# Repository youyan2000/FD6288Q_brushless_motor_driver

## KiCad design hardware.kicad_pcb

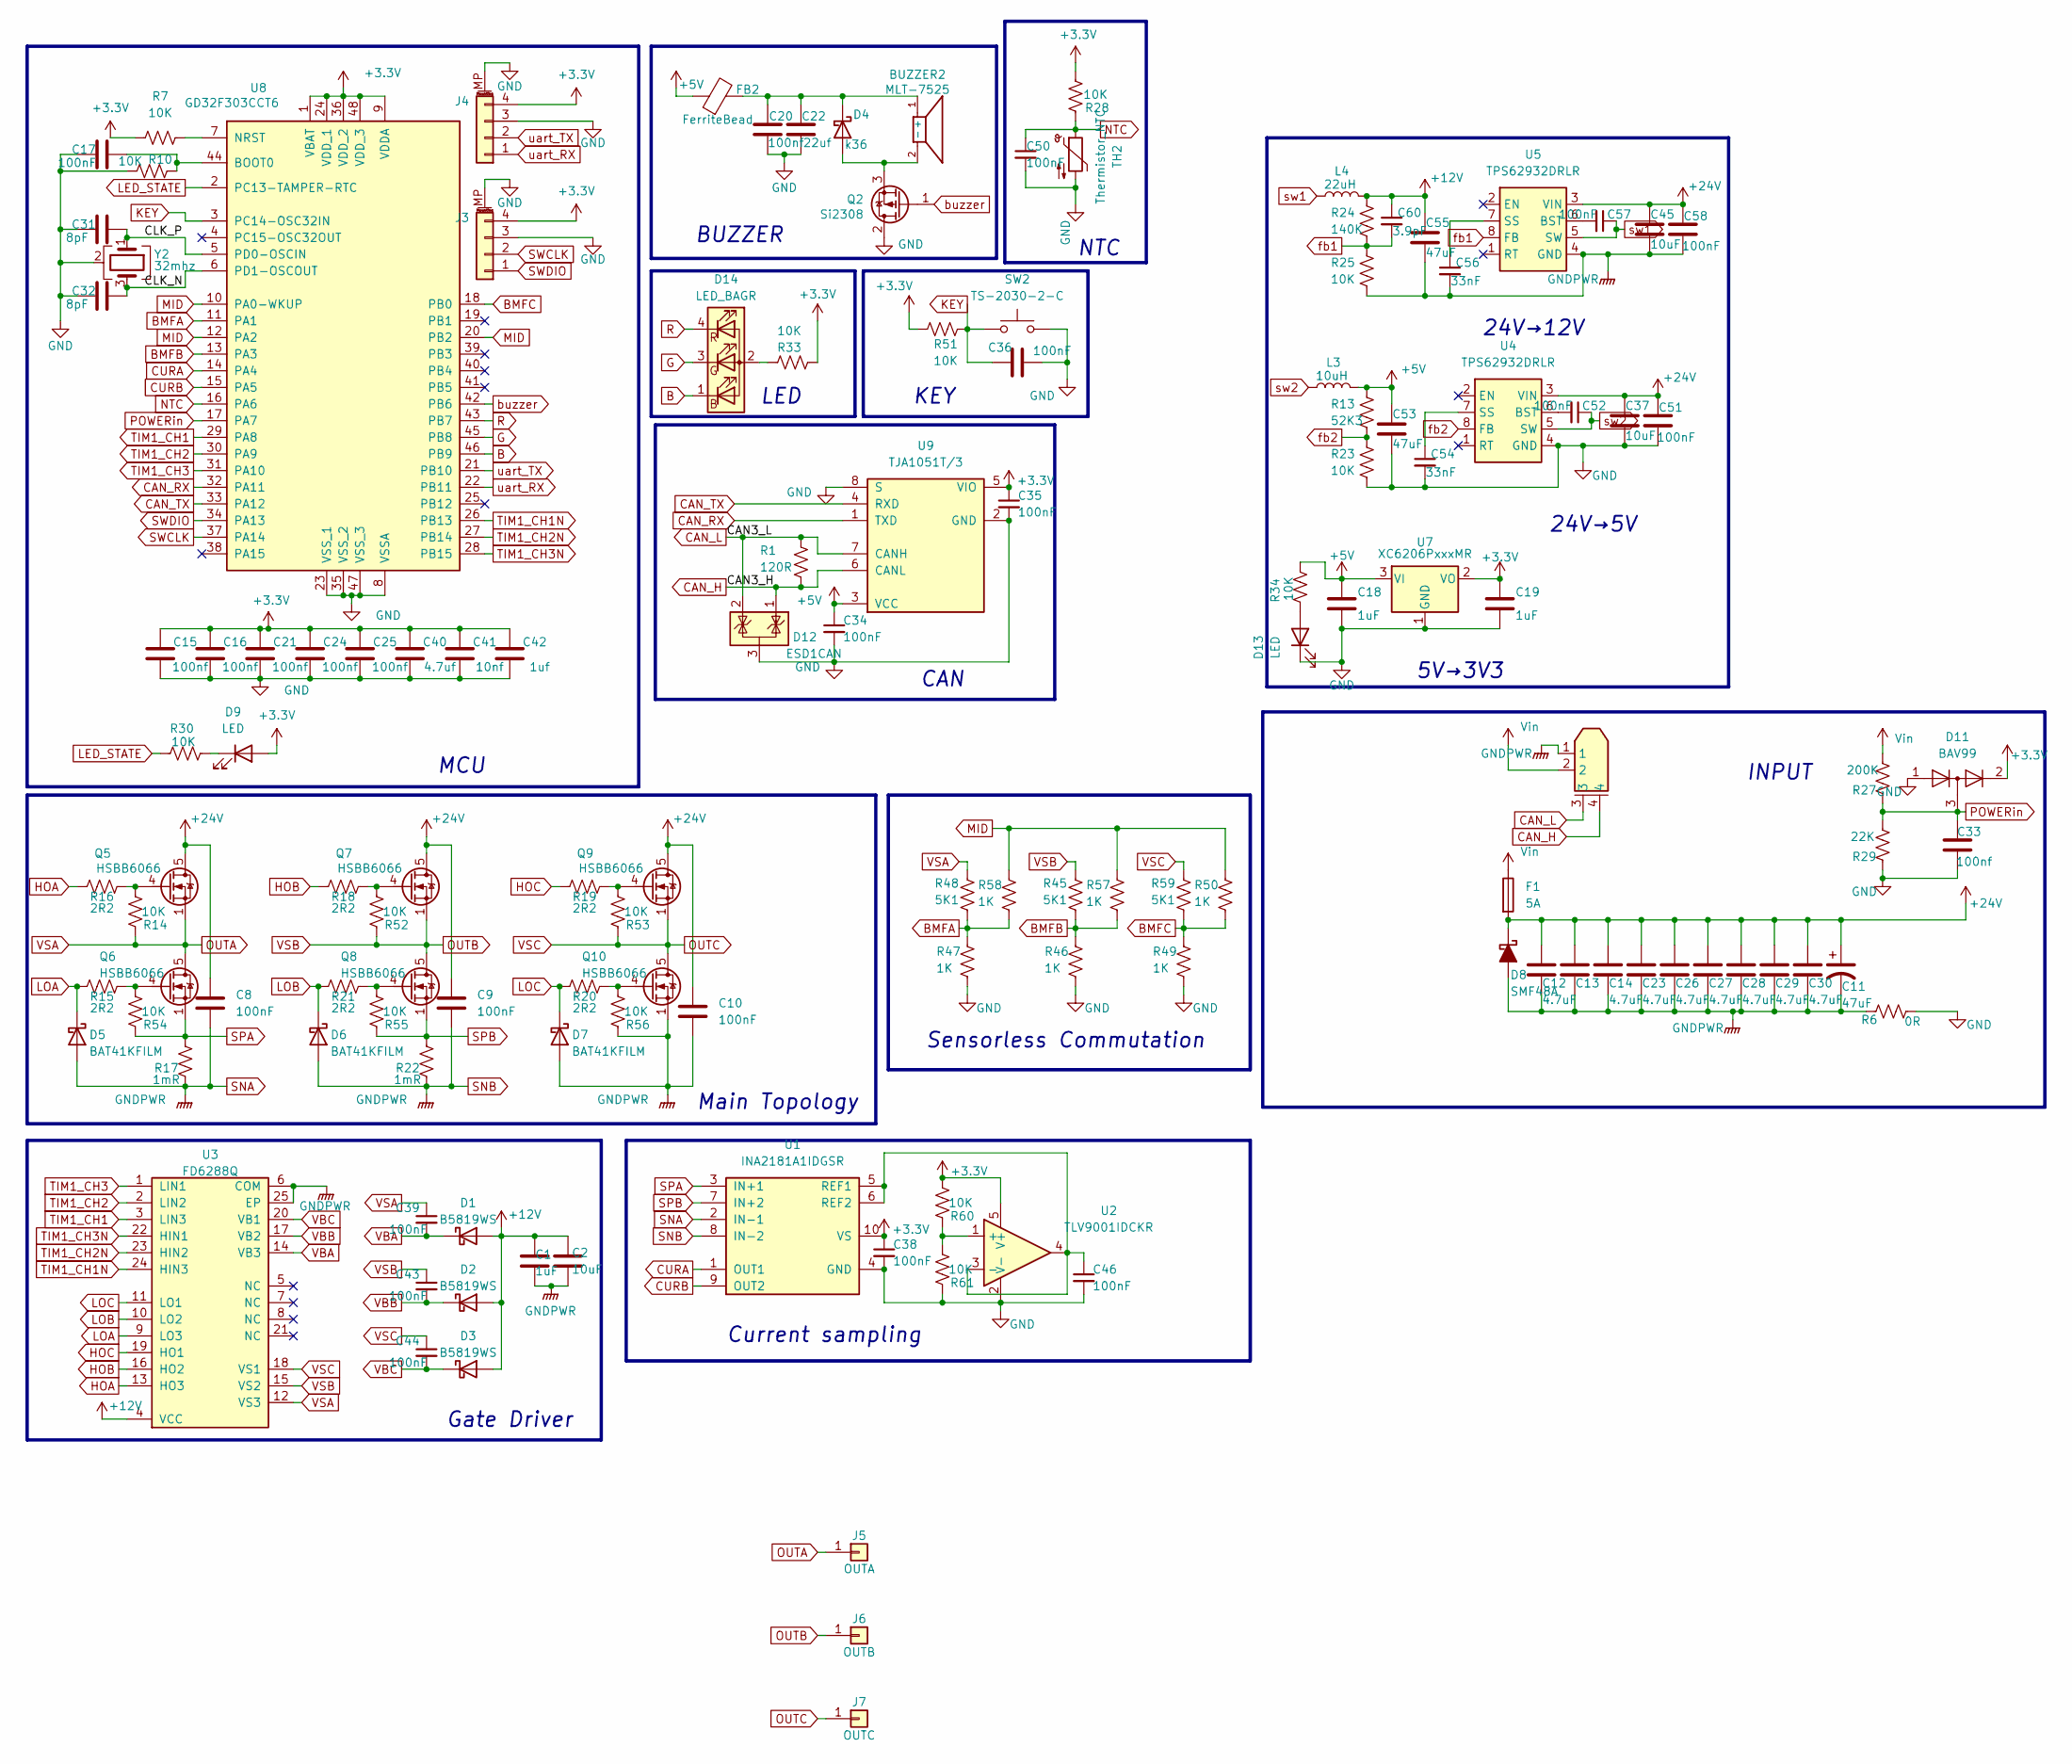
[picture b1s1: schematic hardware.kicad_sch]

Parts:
BUZZER2: MLT-7525; voltage 2.5 V; voltage_rating 3.6 V; MPN MLT-7525
C1: 1uF; C_0805_2012Metric
C2: 10uF; C_0805_2012Metric
C8, C9, C10, C51, C58: 100nF; C_0805_2012Metric
C11: 47uF; CP_Radial_D6.3mm_P2.50mm
C12, C13, C14, C23, C26, C27, C28, C29, C30: 4.7uF; C_0805_2012Metric
C15, C16, C20, C21, C24, C25, C33: 100nf; C_0603_1608Metric_Pad1.08x0.95mm_HandSolder
C17: 100nF; C_0603_1608Metric_Pad1.08x0.95mm_HandSolder
C18, C19: 1uF; C_0603_1608Metric_Pad1.08x0.95mm_HandSolder
C22: 22uf; C_0603_1608Metric_Pad1.08x0.95mm_HandSolder
C31, C32: 8pF; C_0603_1608Metric_Pad1.08x0.95mm_HandSolder
C34, C35, C36, C38, C39, C43, C44, C46, C50, C52, C57: 100nF; C_0603_1608Metric
C37, C45: 10uF; C_1206_3216Metric
C40: 4.7uf; C_0603_1608Metric_Pad1.08x0.95mm_HandSolder
C41: 10nf; C_0603_1608Metric_Pad1.08x0.95mm_HandSolder
C42: 1uf; C_0603_1608Metric_Pad1.08x0.95mm_HandSolder
C53, C55: 47uF; C_1206_3216Metric
C54, C56: 33nF; C_0603_1608Metric
C60: 3.9pF; C_0603_1608Metric
D1, D2, D3: B5819WS; MPN B5819WS
D4: k36; D_SOD-123F
D5, D6, D7: BAT41KFILM; voltage_rating 100 V; MPN BAT41KFILM
D8: SMF48A; MPN SMF48A
D9, D13: LED; LED_0603_1608Metric
D11: BAV99; MPN BAV99
D12: ESD1CAN; SOT-23
D14: LED_BAGR; LED_RGB_1210
F1: 5A; Fuse_1812_4532Metric_Pad1.30x3.40mm_HandSolder
FB2: FerriteBead; L_0603_1608Metric
J2: XT30PW(2+2)-M.G.B; AMASS_XT30PW_2PLUS2__M_G_B; MPN XT30PW(2+2)-M.G.B; LCSC Part C19268030
J3, J4: Conn_01x04; Molex_CLIK-Mate_502386-0470_1x04-1MP_P1.25mm_Horizontal
J5: OUTA; SolderWire-2sqmm_1x01_D2mm_OD3.9mm
J6: OUTB; SolderWire-2sqmm_1x01_D2mm_OD3.9mm
J7: OUTC; SolderWire-2sqmm_1x01_D2mm_OD3.9mm
L3: 10uH; L_APV_ANR4020
L4: 22uH; L_APV_ANR4020
Q2: Si2308; SOT-23
Q5, Q6, Q7, Q8, Q9, Q10: HSBB6066; TDSON-8-1
R1: 120R
R6: 0R; R_0805_2012Metric
R7, R10, R33, R51: 10K; R_0603_1608Metric_Pad0.98x0.95mm_HandSolder
R13: 52K3; R_0603_1608Metric
R14, R23, R25, R28, R30, R34, R52, R53, R54, R55, R56, R60, R61: 10K; R_0603_1608Metric
R15, R16, R18, R19, R20, R21: 2R2; C_0603_1608Metric
R17, R22: 1mR; R_1206_3216Metric
R24: 140K; R_0603_1608Metric
R27: 200K; C_0603_1608Metric
R29: 22K; C_0603_1608Metric
R45, R48, R59: 5K1; R_0603_1608Metric
R46, R47, R49, R50, R57, R58: 1K; R_0603_1608Metric
SW2: TS-2030-2-C; SW_Push_SPST_SMD_ST1185S_4x3mm_P4.4mm; voltage_rating 12 V; MPN TS-2030-2-C
TH2: Thermistor_NTC; R_Axial_DIN0204_L3.6mm_D1.6mm_P1.90mm_Vertical
U1: INA2181A1IDGSR; MPN INA2181A1IDGSR
U2: TLV9001IDCKR; MPN TLV9001IDCKR
U3: FD6288Q; voltage 5 V; MPN FD6288Q
U4, U5: TPS62932DRLR; MPN TPS62932DRLR
U7: XC6206PxxxMR; SOT-23-3
U8: GD32F303CCT6; MPN GD32F303CCT6
U9: TJA1051T/3; TJA1051T_3; MPN TJA1051T/3
Y2: 32mhz; Crystal_SMD_3225-4Pin_3.2x2.5mm

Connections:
+3.3V: C15.1, C16.1, C19.2, C21.1, C24.1, C25.1, C35.1, C38.1, C40.1, C41.1, C42.1, D9.2 (A), D11.2 (K), J3.4, J4.4, R7.2, R28.2, R33.2, R51.2, R60.2, U1.10 (VS), U2.5 (V+), U7.2 (VO), U8.1 (VBAT), U8.9 (VDDA), U8.24 (VDD_1), U8.36 (VDD_2), U8.48 (VDD_3), U9.5 (VIO)
+5V: C18.2, C34.1, C53.1, FB2.1, L3.2, R13.1, R34.1, U7.3 (VI), U9.3 (VCC)
+12V: C1.1, C2.1, C55.1, C60.1, D1.1 (A), D2.1 (A), D3.1 (A), L4.2, R24.1, U3.4 (VCC)
+24V: C8.1, C9.1, C10.1, C11.1, C12.1, C13.1, C14.1, C23.1, C26.1, C27.1, C28.1, C29.1, C30.1, C37.1, C45.1, C51.1, C58.1, D8.1 (K), F1.2, Q5.5 (D), Q7.5 (D), Q9.5 (D), U4.3 (VIN), U5.3 (VIN)
/CLK_N: C32.1, U8.6 (PD1-OSCOUT), Y2.3
/CLK_P: C31.1, U8.5 (PD0-OSCIN), Y2.1
B: D14.1 (BK), U8.46 (PB9)
BMFA: R47.1, R48.2, R58.2, U8.11 (PA1)
BMFB: R45.2, R46.1, R57.2, U8.13 (PA3)
BMFC: R49.1, R50.2, R59.2, U8.18 (PB0)
CAN_H: D12.1 (K), J2.4, R1.2, U9.6 (CANL)
CAN_L: D12.2 (K), J2.3, R1.1, U9.7 (CANH)
CAN_RX: U8.32 (PA11), U9.1 (TXD)
CAN_TX: U8.33 (PA12), U9.4 (RXD)
CURA: U1.1 (OUT1), U8.14 (PA4)
CURB: U1.9 (OUT2), U8.15 (PA5)
G: D14.3 (GK), U8.45 (PB8)
GND: C15.2, C16.2, C17.2, C18.1, C19.1, C20.2, C21.2, C22.1, C24.2, C25.2, C31.2, C32.2, C33.2, C34.2, C35.2, C36.1, C37.2, C38.2, C40.2, C41.2, C42.2, C46.2, C50.2, C51.2, C53.2, C54.2, D11.1 (A), D12.3 (A), D13.1 (K), J3.3, J3.MP (MountPin), J4.3, J4.MP (MountPin), Q2.2 (D), R6.2, R10.2, R23.2, R29.1, R46.2, R47.2, R49.2, R61.1, SW2.2, TH2.2, U1.4 (GND), U2.2 (V-), U4.4 (GND), U7.1 (GND), U8.8 (VSSA), U8.23 (VSS_1), U8.35 (VSS_2), U8.47 (VSS_3), U9.2 (GND), U9.8 (S), Y2.2 (G), Y2.4 (G)
HOA: R16.1, U3.13 (HO3)
HOB: R18.1, U3.16 (HO2)
HOC: R19.1, U3.19 (HO1)
KEY: C36.2, R51.1, SW2.1, U8.3 (PC14-OSC32IN)
LED_STATE: R30.2, U8.2 (PC13-TAMPER-RTC)
LOA: D5.1 (K), R15.1, U3.9 (LO3)
LOB: D6.1 (K), R21.1, U3.10 (LO2)
LOC: D7.1 (K), R20.1, U3.11 (LO1)
MID: R50.1, R57.1, R58.1, U8.10 (PA0-WKUP), U8.12 (PA2), U8.20 (PB2)
NTC: C50.1, R28.1, TH2.1, U8.16 (PA6)
unnamed: BUZZER2.1 (+), C20.1, C22.2, D4.1 (K), FB2.2
unnamed: BUZZER2.2 (-), D4.2 (A), Q2.3 (S)
unnamed: D9.1 (K), R30.1
unnamed: D13.2 (A), R34.2
unnamed: D14.2 (A), R33.1
unnamed: Q5.4 (G), R14.2, R16.2
unnamed: Q6.4 (G), R15.2, R54.2
unnamed: Q7.4 (G), R18.2, R52.2
unnamed: Q8.4 (G), R21.2, R55.2
unnamed: Q9.4 (G), R19.2, R53.2
unnamed: Q10.4 (G), R20.2, R56.2
unnamed: C46.1, U1.5 (REF1), U1.6 (REF2), U2.3 (-), U2.4
unnamed: R60.1, R61.2, U2.1 (+)
unnamed: C52.2, U4.6 (BST)
unnamed: C54.1, U4.7 (SS)
unnamed: C57.2, U5.6 (BST)
unnamed: C56.1, U5.7 (SS)
unnamed: C17.1, R10.1, U8.44 (BOOT0)
unnamed: R7.1, U8.7 (NRST)
OUTA: C39.1, J5.1 (Pin_1_1), Q5.1 (S), Q5.2 (S), Q5.3 (S), Q6.5 (D), R14.1, R48.1, U3.12 (VS3)
OUTB: C43.1, J6.1 (Pin_1_1), Q7.1 (S), Q7.2 (S), Q7.3 (S), Q8.5 (D), R45.1, R52.1, U3.15 (VS2)
OUTC: C44.1, J7.1 (Pin_1_1), Q9.1 (S), Q9.2 (S), Q9.3 (S), Q10.5 (D), R53.1, R59.1, U3.18 (VS1)
POWERin: C33.1, D11.3 (C), R27.1, R29.2, U8.17 (PA7)
R: D14.4 (RK), U8.43 (PB7)
SNA: C1.2, C2.2, C8.2, C9.2, C10.2, C11.2, C12.2, C13.2, C14.2, C23.2, C26.2, C27.2, C28.2, C29.2, C30.2, C45.2, C55.2, C56.2, C58.2, D5.2 (A), D6.2 (A), D7.2 (A), D8.2 (A), J2.1, Q10.1 (S), Q10.2 (S), Q10.3 (S), R6.1, R17.2, R22.2, R25.2, R56.1, U1.2 (IN-1), U1.8 (IN-2), U3.6 (COM), U3.25 (EP), U5.4 (GND)
SPA: Q6.1 (S), Q6.2 (S), Q6.3 (S), R17.1, R54.1, U1.3 (IN+1)
SPB: Q8.1 (S), Q8.2 (S), Q8.3 (S), R22.1, R55.1, U1.7 (IN+2)
SWCLK: J3.2, U8.37 (PA14)
SWDIO: J3.1, U8.34 (PA13)
TIM1_CH1: U3.3 (LIN3), U8.29 (PA8)
TIM1_CH1N: U3.24 (HIN3), U8.26 (PB13)
TIM1_CH2: U3.2 (LIN2), U8.30 (PA9)
TIM1_CH2N: U3.23 (HIN2), U8.27 (PB14)
TIM1_CH3: U3.1 (LIN1), U8.31 (PA10)
TIM1_CH3N: U3.22 (HIN1), U8.28 (PB15)
VBA: C39.2, D1.2 (K), U3.14 (VB3)
VBB: C43.2, D2.2 (K), U3.17 (VB2)
VBC: C44.2, D3.2 (K), U3.20 (VB1)
Vin: F1.1, J2.2, R27.2
buzzer: Q2.1 (G), U8.42 (PB6)
fb1: C60.2, R24.2, R25.1, U5.8 (FB)
fb2: R13.2, R23.1, U4.8 (FB)
sw1: C57.1, L4.1, U5.5 (SW)
sw2: C52.1, L3.1, U4.5 (SW)
uart_RX: J4.1, U8.22 (PB11)
uart_TX: J4.2, U8.21 (PB10)

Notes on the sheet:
CAN
Main Topology
MCU
NTC
5V→3V3
Gate Driver
Current sampling
Sensorless Commutation
KEY
24V→5V
24V→12V
INPUT
LED
BUZZER

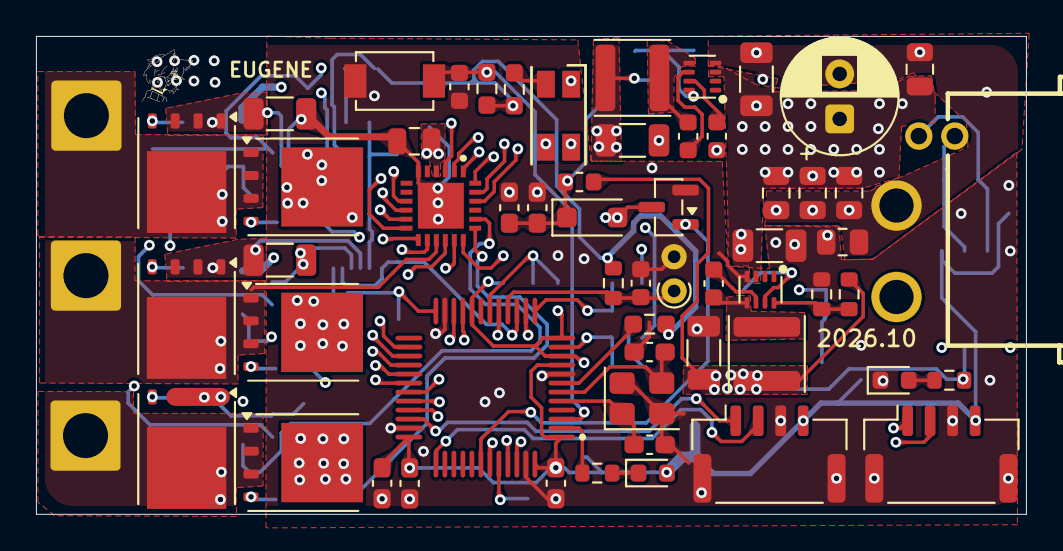
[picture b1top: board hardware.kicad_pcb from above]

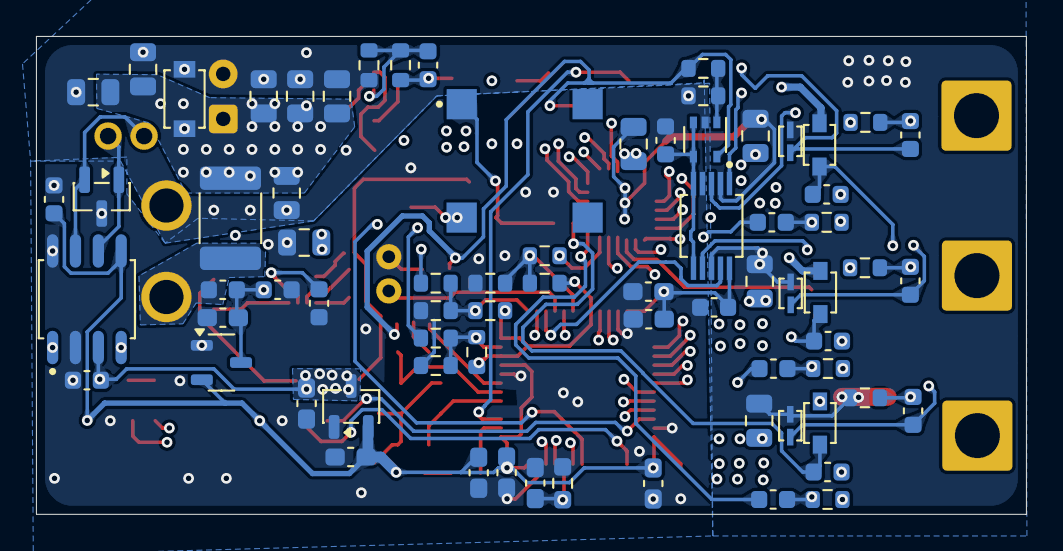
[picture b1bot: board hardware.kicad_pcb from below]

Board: 6 copper layers, 55.0 x 26.6 mm, 132 parts (72 on the bottom side), 74 nets.
